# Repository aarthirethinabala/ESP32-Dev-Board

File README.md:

# ESP32 Development Board
Custom ESP32 development board designed and routed in KiCad, including schematic design, component footprint assignment, PCB layout, routing and 3D visualization.

## Project Status
Completed

## Overview
This project is a custom ESP32 development board based on the ESP32-WROOM module.
The board was designed from the schematic stage through PCB layout and routing, including power regulation, USB-to-UART communication, boot/reset controls, GPIO headers, and supporting components.

## Tools Used
- KiCad
- PCB Editor
- Schematic Editor
- 3D Viewer

## Board Features
- ESP32-WROOM module
- USB-to-UART interface
- 5V to 3.3V voltage regulation
- Boot and reset controls
- GPIO headers
- Status LED
- Two-layer PCB
- Ground copper zones

## Design Process
- Studied the reference ESP32 board circuitry
- Converted the reference into hierarchical KiCad sheets
- Assigned footprints
- Designed component placement independently
- Routed the PCB manually
- Added vias and layer changes where required
- Checked the design with ERC/DRC
- Corrected connectivity and layout issues

## Project Images
### Root Schematic

### Page 2 Schematic

### PCB Layout

### 3D Front View 

### 3D Back View

## What I Learned
- Hierarchical schematic organization
- ESP32 development-board architecture
- Footprint selection
- Two-layer PCB design
- Via usage and layer transitions
- Ground planes/zones
- DRC troubleshooting
- Independent component placement and routing

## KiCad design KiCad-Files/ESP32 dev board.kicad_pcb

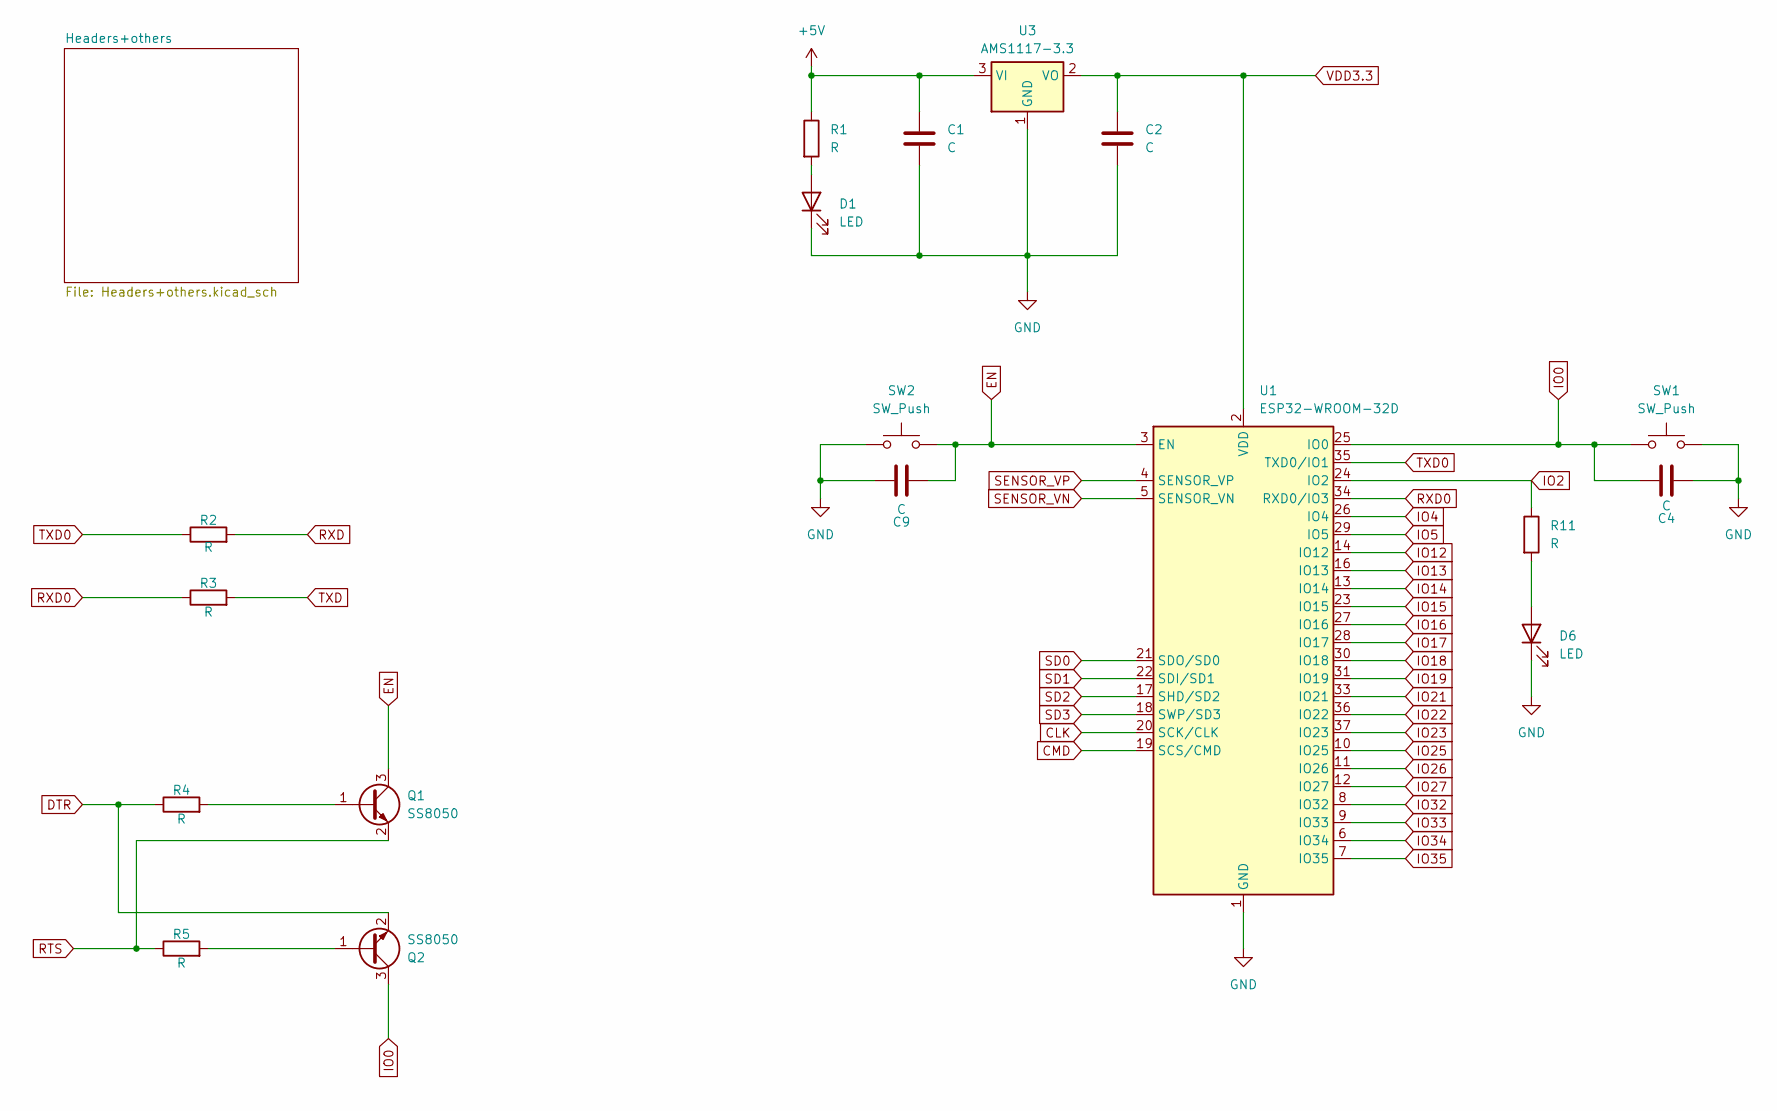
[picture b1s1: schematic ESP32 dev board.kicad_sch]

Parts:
C1, C2, C4, C9: C; C_0603_1608Metric
D1, D6: LED; LED_0805_2012Metric
Q1, Q2: SS8050; SOT-23
R1, R2, R3, R4, R5, R11: R; R_0603_1608Metric
SW1, SW2: SW_Push; SW_Push_1P1T_NO_E-Switch_TL3301NxxxxxG
U1: ESP32-WROOM-32D
U3: AMS1117-3.3; SOT-223-3_TabPin2

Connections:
+5V: C1.1, R1.1, U3.3 (VI); also elsewhere on the board
CLK: U1.20 (SCK/CLK); also elsewhere on the board
CMD: U1.19 (SCS/CMD); also elsewhere on the board
DTR: Q2.2 (E), R4.1; also elsewhere on the board
EN: C9.2, Q1.3 (C), SW2.2, U1.3 (EN); also elsewhere on the board
GND: C1.2, C2.2, C4.2, C9.1, D1.1 (K), D6.1 (K), SW1.2, SW2.1, U1.1 (GND), U1.15 (GND), U1.38 (GND), U1.39 (GND), U3.1 (GND); also elsewhere on the board
IO0: C4.1, Q2.3 (C), SW1.1, U1.25 (IO0); also elsewhere on the board
IO2: R11.1, U1.24 (IO2); also elsewhere on the board
IO4: U1.26 (IO4); also elsewhere on the board
IO5: U1.29 (IO5); also elsewhere on the board
IO12: U1.14 (IO12); also elsewhere on the board
IO13: U1.16 (IO13); also elsewhere on the board
IO14: U1.13 (IO14); also elsewhere on the board
IO15: U1.23 (IO15); also elsewhere on the board
IO16: U1.27 (IO16); also elsewhere on the board
IO17: U1.28 (IO17); also elsewhere on the board
IO18: U1.30 (IO18); also elsewhere on the board
IO19: U1.31 (IO19); also elsewhere on the board
IO21: U1.33 (IO21); also elsewhere on the board
IO22: U1.36 (IO22); also elsewhere on the board
IO23: U1.37 (IO23); also elsewhere on the board
IO25: U1.10 (IO25); also elsewhere on the board
IO26: U1.11 (IO26); also elsewhere on the board
IO27: U1.12 (IO27); also elsewhere on the board
IO32: U1.8 (IO32); also elsewhere on the board
IO33: U1.9 (IO33); also elsewhere on the board
IO34: U1.6 (IO34); also elsewhere on the board
IO35: U1.7 (IO35); also elsewhere on the board
unnamed: D1.2 (A), R1.2
unnamed: D6.2 (A), R11.2
unnamed: Q1.1 (B), R4.2
unnamed: Q2.1 (B), R5.2
RTS: Q1.2 (E), R5.1; also elsewhere on the board
RXD: R2.2; also elsewhere on the board
RXD0: R3.1, U1.34 (RXD0/IO3); also elsewhere on the board
SD0: U1.21 (SDO/SD0); also elsewhere on the board
SD1: U1.22 (SDI/SD1); also elsewhere on the board
SD2: U1.17 (SHD/SD2); also elsewhere on the board
SD3: U1.18 (SWP/SD3); also elsewhere on the board
SENSOR_VN: U1.5 (SENSOR_VN); also elsewhere on the board
SENSOR_VP: U1.4 (SENSOR_VP); also elsewhere on the board
TXD: R3.2; also elsewhere on the board
TXD0: R2.1, U1.35 (TXD0/IO1); also elsewhere on the board
VDD3.3: C2.1, U1.2 (VDD), U3.2 (VO); also elsewhere on the board

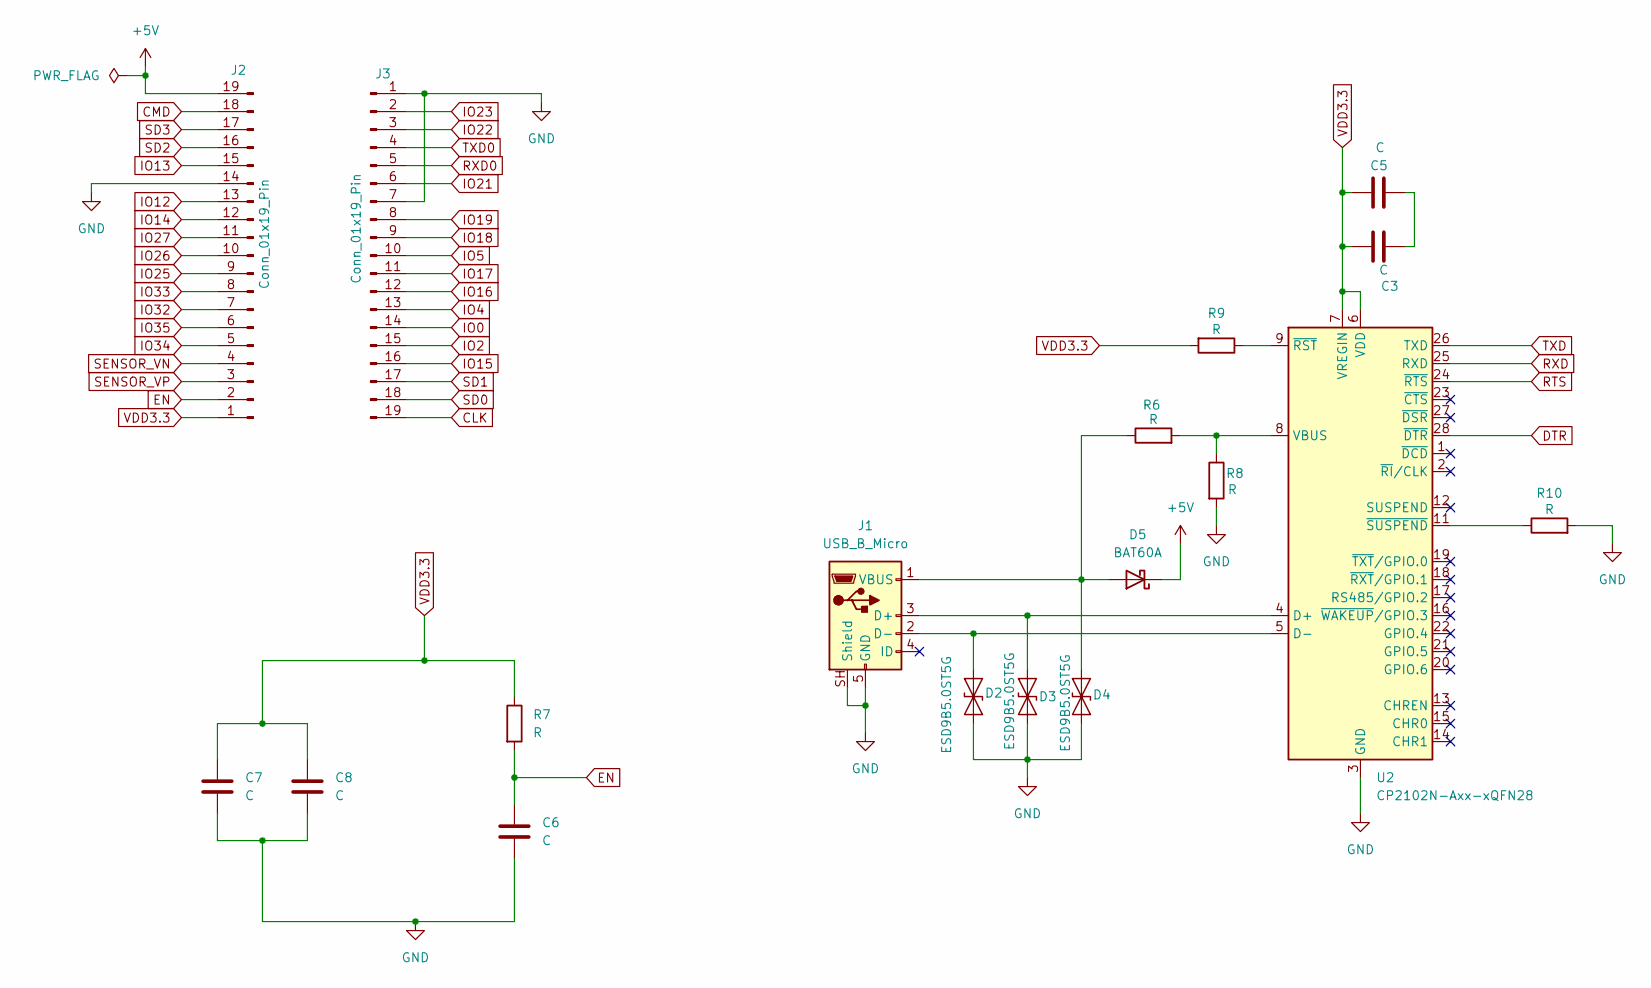
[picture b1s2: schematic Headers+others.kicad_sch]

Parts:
C3, C5, C6, C7, C8: C; C_0603_1608Metric
D2, D3, D4: ESD9B5.0ST5G; D_SOD-923
D5: BAT60A; D_SOD-323
J1: USB_B_Micro; USB_Micro-B_Molex-105133-0001
J2, J3: Conn_01x19_Pin; PinHeader_1x19_P2.54mm_Vertical
R6, R7, R8, R9, R10: R; R_0603_1608Metric
U2: CP2102N-Axx-xQFN28; QFN-28-1EP_5x5mm_P0.5mm_EP3.35x3.35mm

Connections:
+5V: D5.1 (K), J2.19; also elsewhere on the board
CLK: J3.19; also elsewhere on the board
CMD: J2.18; also elsewhere on the board
DTR: U2.28 (~DTR); also elsewhere on the board
EN: C6.1, J2.2, R7.2; also elsewhere on the board
GND: C6.2, C7.2, C8.2, D2.1 (A1), D3.1 (A1), D4.1 (A1), J1.5 (GND), J1.SH (Shield), J2.14, J3.1, J3.7, R8.2, R10.2, U2.3 (GND), U2.29 (GND); also elsewhere on the board
IO0: J3.14; also elsewhere on the board
IO2: J3.15; also elsewhere on the board
IO4: J3.13; also elsewhere on the board
IO5: J3.10; also elsewhere on the board
IO12: J2.13; also elsewhere on the board
IO13: J2.15; also elsewhere on the board
IO14: J2.12; also elsewhere on the board
IO15: J3.16; also elsewhere on the board
IO16: J3.12; also elsewhere on the board
IO17: J3.11; also elsewhere on the board
IO18: J3.9; also elsewhere on the board
IO19: J3.8; also elsewhere on the board
IO21: J3.6; also elsewhere on the board
IO22: J3.3; also elsewhere on the board
IO23: J3.2; also elsewhere on the board
IO25: J2.9; also elsewhere on the board
IO26: J2.10; also elsewhere on the board
IO27: J2.11; also elsewhere on the board
IO32: J2.7; also elsewhere on the board
IO33: J2.8; also elsewhere on the board
IO34: J2.5; also elsewhere on the board
IO35: J2.6; also elsewhere on the board
unnamed: C3.1, C5.1
unnamed: D2.2 (A2), J1.2 (D-), U2.5 (D-)
unnamed: D3.2 (A2), J1.3 (D+), U2.4 (D+)
unnamed: D4.2 (A2), D5.2 (A), J1.1 (VBUS), R6.1
unnamed: R6.2, R8.1, U2.8 (VBUS)
unnamed: R9.1, U2.9 (~RST)
unnamed: R10.1, U2.11 (~SUSPEND)
RTS: U2.24 (~RTS); also elsewhere on the board
RXD: U2.25 (RXD); also elsewhere on the board
RXD0: J3.5; also elsewhere on the board
SD0: J3.18; also elsewhere on the board
SD1: J3.17; also elsewhere on the board
SD2: J2.16; also elsewhere on the board
SD3: J2.17; also elsewhere on the board
SENSOR_VN: J2.4; also elsewhere on the board
SENSOR_VP: J2.3; also elsewhere on the board
TXD: U2.26 (TXD); also elsewhere on the board
TXD0: J3.4; also elsewhere on the board
VDD3.3: C3.2, C5.2, C7.1, C8.1, J2.1, R7.1, R9.2, U2.6 (VDD), U2.7 (VREGIN); also elsewhere on the board

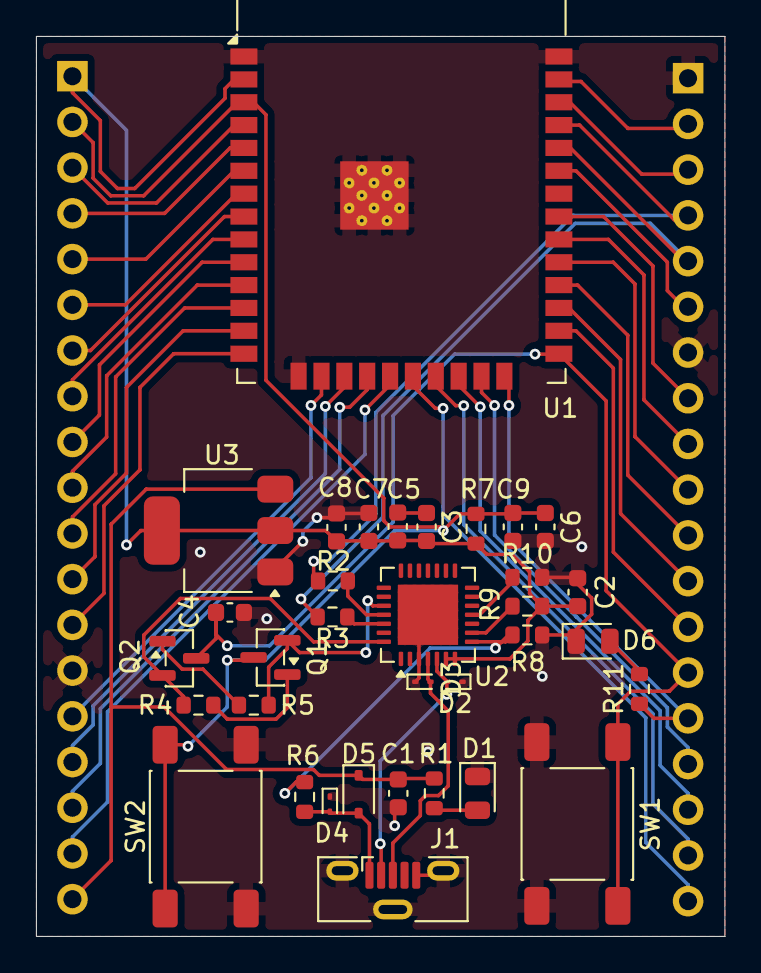
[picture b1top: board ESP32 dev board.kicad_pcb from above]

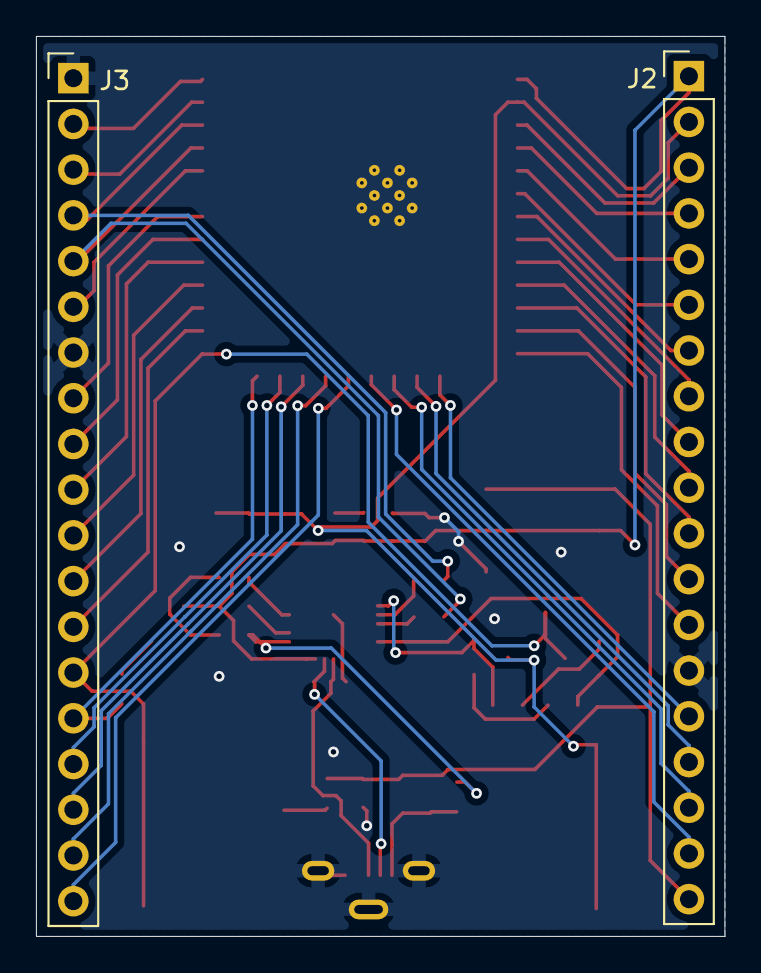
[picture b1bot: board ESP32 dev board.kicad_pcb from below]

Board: 2 copper layers, 38.2 x 50.0 mm, 36 parts (2 on the bottom side), 51 nets.
